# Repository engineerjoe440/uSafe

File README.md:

# uSafe

*A simple pin-based lock-box for education.*

## Bill of Materials

| **Component** | **Link** |
|---------------|----------|
| PS1           | [DigiKey](https://www.digikey.com/en/products/detail/xp-power/IZB0312S3V3/17141038) |

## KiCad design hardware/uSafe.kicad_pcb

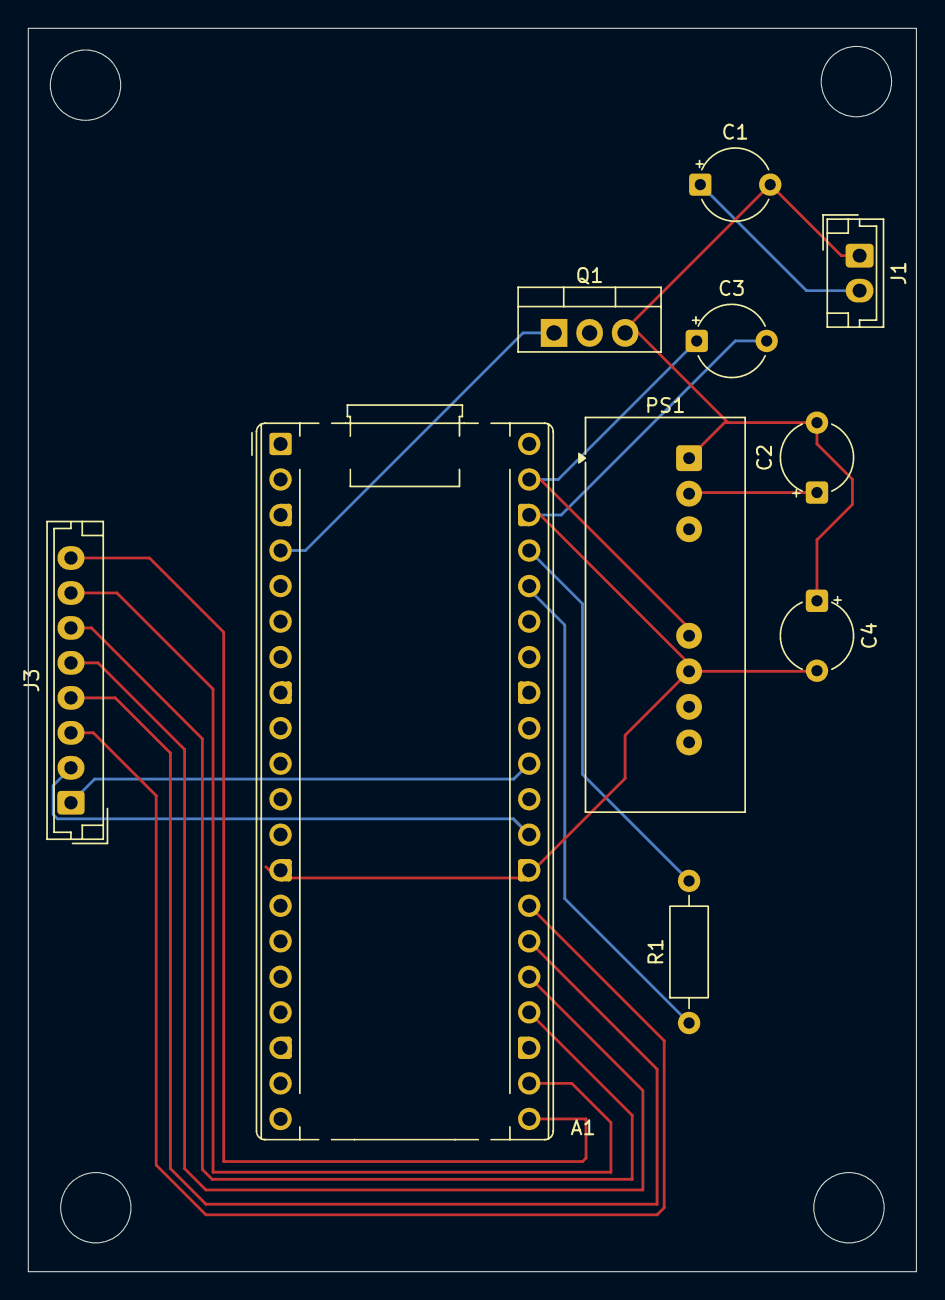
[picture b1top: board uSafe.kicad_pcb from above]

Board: 2 copper layers, 63.5 x 88.9 mm, 10 parts (0 on the bottom side), 16 nets.

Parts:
A1: RaspberryPi_Pico_W; RaspberryPi_Pico_Common_THT
C1, C2: 4.7uF; CP_Radial_Tantal_D5.0mm_P5.00mm
C3: 100uF; CP_Radial_Tantal_D5.0mm_P5.00mm
C4: 1nF; CP_Radial_Tantal_D5.0mm_P5.00mm
J1: Conn_01x02_Socket; JST_EH_B2B-EH-A_1x02_P2.50mm_Vertical
J3: Conn_01x08_Pin; JST_EH_B8B-EH-A_1x08_P2.50mm_Vertical
PS1: ITX4824SA-R; Converter_DCDC_XP_POWER-ITxxxxxS_THT
Q1: BUZ11; TO-220-3_Vertical
R1: R; R_Axial_DIN0207_L6.3mm_D2.5mm_P10.16mm_Horizontal

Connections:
unnamed: A1.36 (3V3), R1.1
unnamed: A1.37 (3V3_EN), R1.2
unnamed: A1.4 (GPIO2), Q1.1 (G)
unnamed: A1.21 (GPIO16), J3.8
unnamed: A1.22 (GPIO17), J3.7
unnamed: A1.24 (GPIO18), J3.6
unnamed: A1.25 (GPIO19), J3.5
unnamed: A1.26 (GPIO20), J3.4
unnamed: A1.27 (GPIO21), J3.3
unnamed: A1.29 (GPIO22), J3.2
unnamed: A1.31 (GPIO26_ADC0), J3.1
unnamed: A1.39 (VSYS), C3.1, PS1.6 (+Vout)
unnamed: C1.2, C2.2, C4.1, J1.1, PS1.1 (-Vin), Q1.3 (S)
unnamed: C1.1, J1.2
unnamed: C2.1, PS1.2 (+Vin)
unnamed: A1.3 (GND), A1.8 (GND), A1.13 (GND), A1.18 (GND), A1.23 (GND), A1.28 (GND), A1.38 (GND), C3.2, C4.2, PS1.7 (-Vout)

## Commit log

2025-12-01 updated readme, started hardware folder
2025-12-01 set up hardware
2025-12-01 link
2025-12-06 started fleshing out hardware
2025-12-06 added keypad connector

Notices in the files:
hardware/uSafe.kicad_pcb:
License: GPL3.0
